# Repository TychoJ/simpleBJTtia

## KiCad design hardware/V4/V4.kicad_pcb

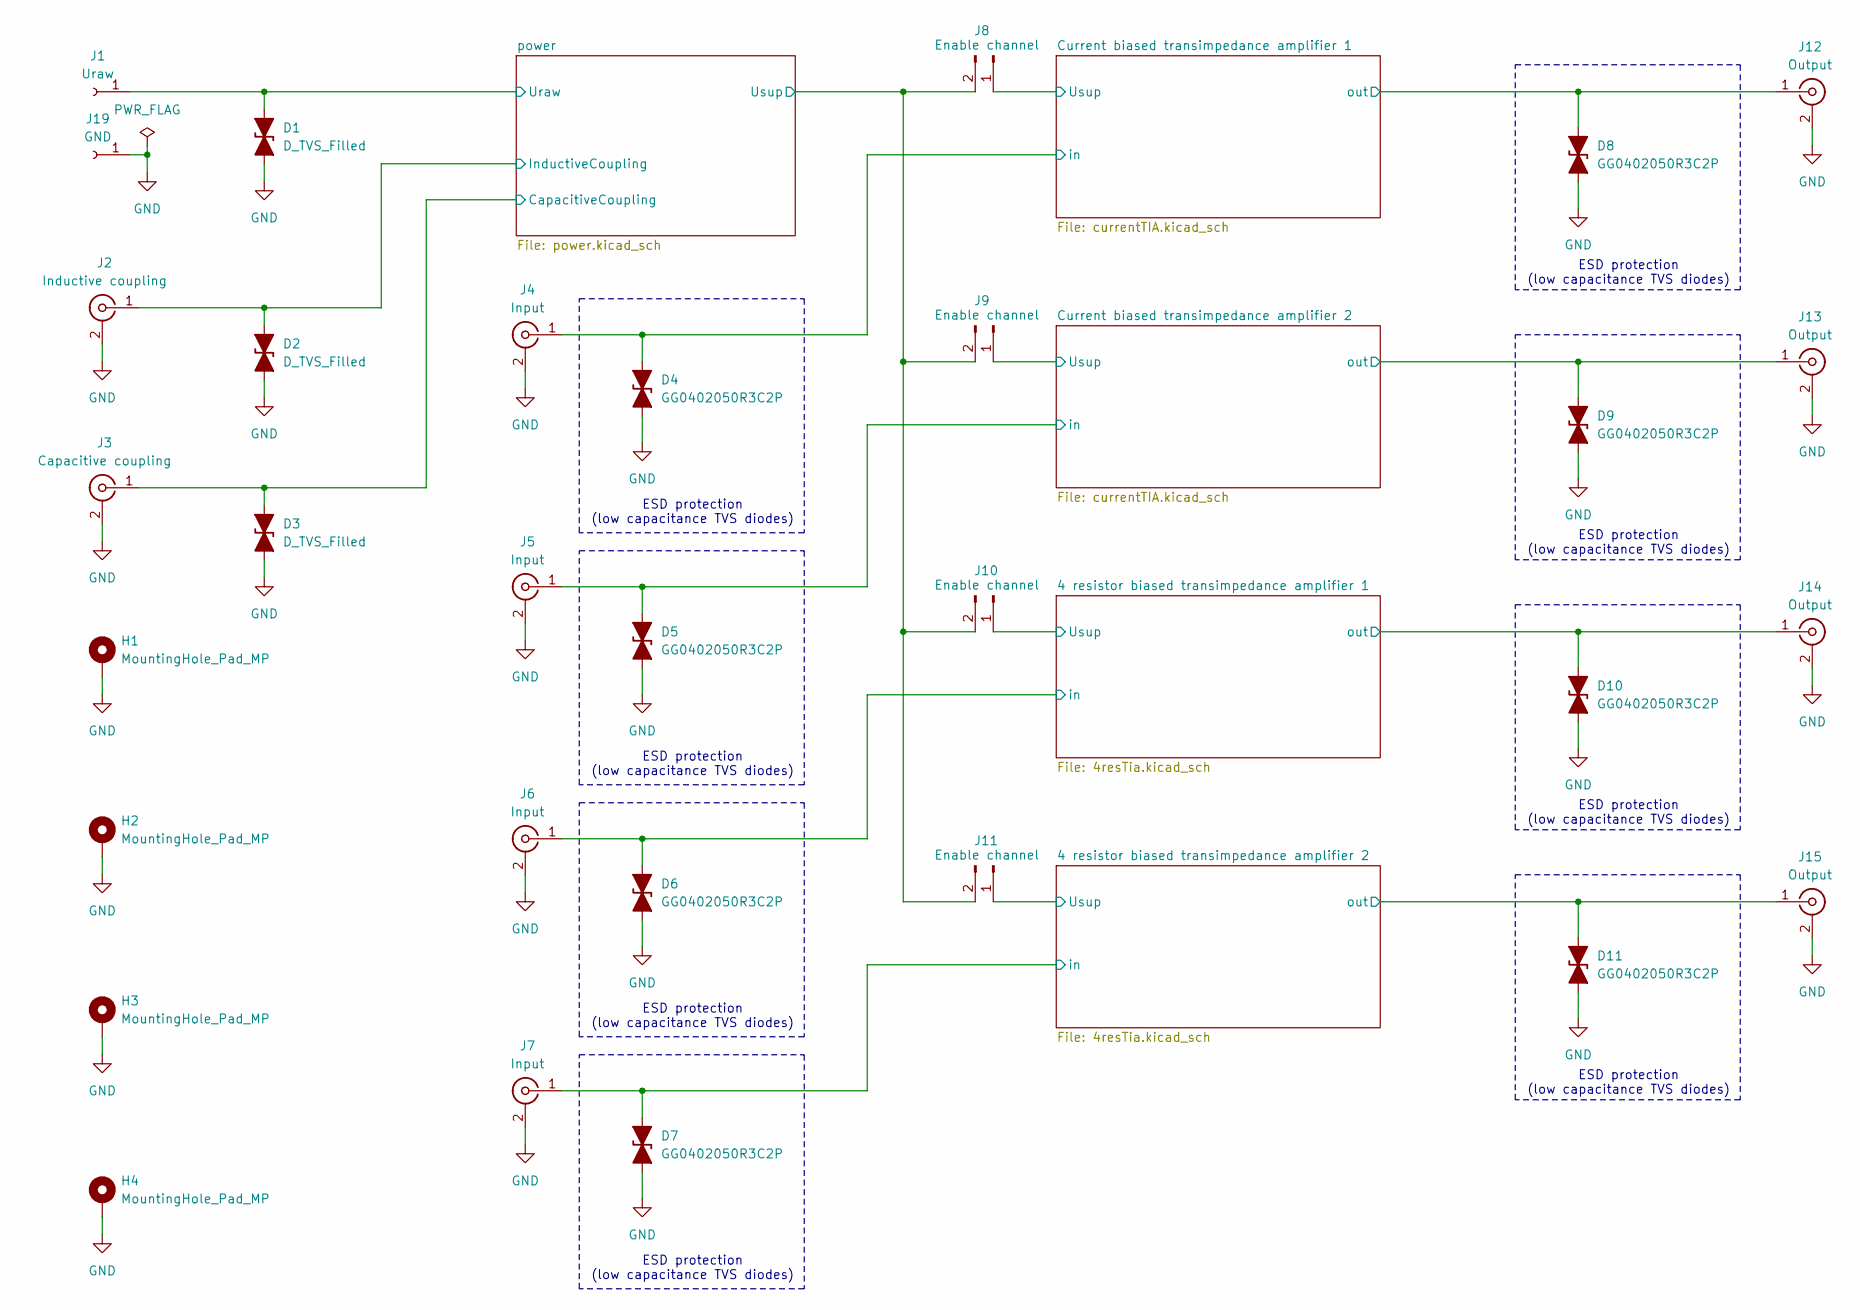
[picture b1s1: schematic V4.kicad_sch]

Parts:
D1, D2, D3: D_TVS_Filled; D_0805_2012Metric
D4, D5, D6, D7, D8, D9, D10, D11: GG0402050R3C2P; D_0402_1005Metric_Pad0.77x0.64mm_HandSolder
H1, H2, H3, H4: MountingHole_Pad_MP; MountingHole_4.3mm_M4_Pad_Via
J1: Uraw; Banana_Jack_1Pin
J2: Inductive coupling; BNC_Amphenol_B6252HB-NPP3G-50_Horizontal
J3: Capacitive coupling; BNC_Amphenol_B6252HB-NPP3G-50_Horizontal
J4, J5, J6, J7: Input; BNC_Amphenol_B6252HB-NPP3G-50_Horizontal
J8, J9, J10, J11: Enable channel; PinHeader_1x02_P2.54mm_Vertical
J12, J13, J14, J15: Output; BNC_Amphenol_B6252HB-NPP3G-50_Horizontal
J19: GND; Banana_Jack_1Pin

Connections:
/4 resistor biased transimpedance amplifier 1/Usup: J10.1; also elsewhere on the board
/4 resistor biased transimpedance amplifier 1/in: D6.2 (A2), J6.1 (In); also elsewhere on the board
/4 resistor biased transimpedance amplifier 1/out: D10.2 (A2), J14.1 (In); also elsewhere on the board
/4 resistor biased transimpedance amplifier 2/Usup: J11.1; also elsewhere on the board
/4 resistor biased transimpedance amplifier 2/in: D7.2 (A2), J7.1 (In); also elsewhere on the board
/4 resistor biased transimpedance amplifier 2/out: D11.2 (A2), J15.1 (In); also elsewhere on the board
/Current biased transimpedance amplifier 1/Usup: J8.1; also elsewhere on the board
/Current biased transimpedance amplifier 1/in: D4.2 (A2), J4.1 (In); also elsewhere on the board
/Current biased transimpedance amplifier 1/out: D8.2 (A2), J12.1 (In); also elsewhere on the board
/Current biased transimpedance amplifier 2/Usup: J9.1; also elsewhere on the board
/Current biased transimpedance amplifier 2/in: D5.2 (A2), J5.1 (In); also elsewhere on the board
/Current biased transimpedance amplifier 2/out: D9.2 (A2), J13.1 (In); also elsewhere on the board
/power/CapacitiveCoupling: D3.2 (A2), J3.1 (In); also elsewhere on the board
/power/InductiveCoupling: D2.2 (A2), J2.1 (In); also elsewhere on the board
/power/Uraw: D1.2 (A2), J1.1; also elsewhere on the board
/power/Usup: J8.2, J9.2, J10.2, J11.2; also elsewhere on the board
GND: D1.1 (A1), D2.1 (A1), D3.1 (A1), D4.1 (A1), D5.1 (A1), D6.1 (A1), D7.1 (A1), D8.1 (A1), D9.1 (A1), D10.1 (A1), D11.1 (A1), H1.MP, H2.MP, H3.MP, H4.MP, J2.2 (Ext), J3.2 (Ext), J4.2 (Ext), J5.2 (Ext), J6.2 (Ext), J7.2 (Ext), J12.2 (Ext), J13.2 (Ext), J14.2 (Ext), J15.2 (Ext), J19.1; also elsewhere on the board

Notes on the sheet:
ESD protection (low capacitance TVS diodes)

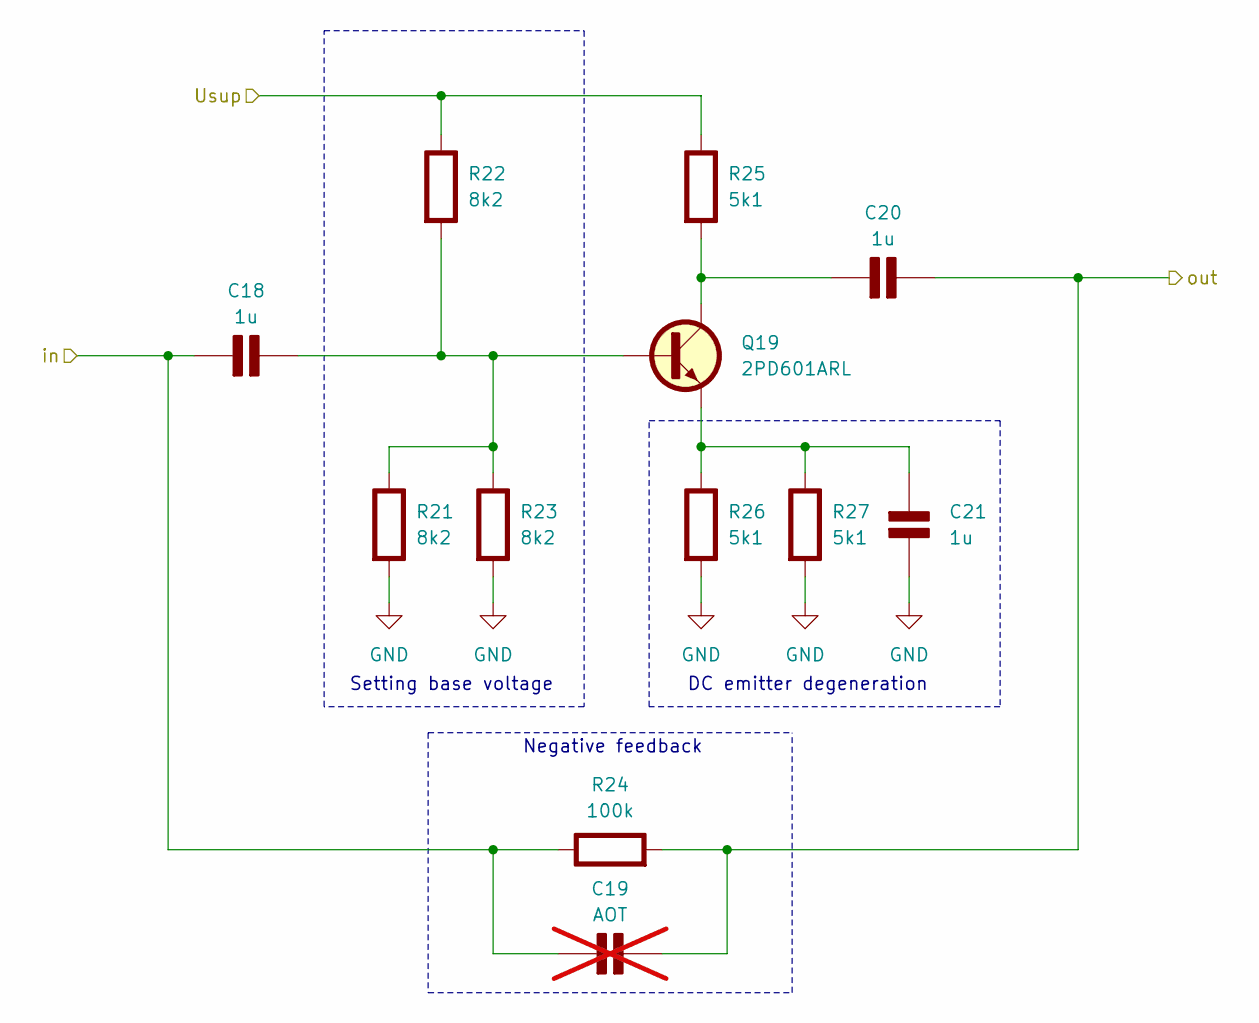
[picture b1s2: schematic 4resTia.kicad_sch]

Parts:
C18, C20, C21: 1u; C_0805_2012Metric; Rating V
C19: AOT; C_0805_2012Metric; Rating V; not fitted
Q19: 2PD601ARL; SOT-23
R21, R22, R23: 8k2; R_0805_2012Metric; Rating W
R24: 100k; R_0805_2012Metric; Rating W
R25, R26, R27: 5k1; R_0805_2012Metric; Rating W

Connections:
/4 resistor biased transimpedance amplifier 1/Usup: R22.1 (+), R25.1 (+); also elsewhere on the board
/4 resistor biased transimpedance amplifier 1/in: C18.1 (+), C19.1 (+), R24.1 (+); also elsewhere on the board
/4 resistor biased transimpedance amplifier 1/out: C19.2 (-), C20.2 (-), R24.2 (-); also elsewhere on the board
GND: C21.2 (-), R21.2 (-), R23.2 (-), R26.2 (-), R27.2 (-); also elsewhere on the board
unnamed: C18.2 (-), Q19.1 (B), R21.1 (+), R22.2 (-), R23.1 (+)
unnamed: C20.1 (+), Q19.3 (C), R25.2 (-)
unnamed: C21.1 (+), Q19.2 (E), R26.1 (+), R27.1 (+)

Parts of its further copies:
C22, C24, C25: 1u; C_0805_2012Metric; Rating V
C23: AOT; C_0805_2012Metric; Rating V; not fitted
Q20: 2PD601ARL; SOT-23
R28, R29, R30: 8k2; R_0805_2012Metric; Rating W
R31: 100k; R_0805_2012Metric; Rating W
R32, R33, R34: 5k1; R_0805_2012Metric; Rating W

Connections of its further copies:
/4 resistor biased transimpedance amplifier 2/Usup: R29.1 (+), R32.1 (+); also elsewhere on the board
/4 resistor biased transimpedance amplifier 2/in: C22.1 (+), C23.1 (+), R31.1 (+); also elsewhere on the board
/4 resistor biased transimpedance amplifier 2/out: C23.2 (-), C24.2 (-), R31.2 (-); also elsewhere on the board
GND: C25.2 (-), R28.2 (-), R30.2 (-), R33.2 (-), R34.2 (-); also elsewhere on the board
unnamed: C22.2 (-), Q20.1 (B), R28.1 (+), R29.2 (-), R30.1 (+)
unnamed: C24.1 (+), Q20.3 (C), R32.2 (-)
unnamed: C25.1 (+), Q20.2 (E), R33.1 (+), R34.1 (+)

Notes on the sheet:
DC emitter degeneration
Negative feedback
Setting base voltage

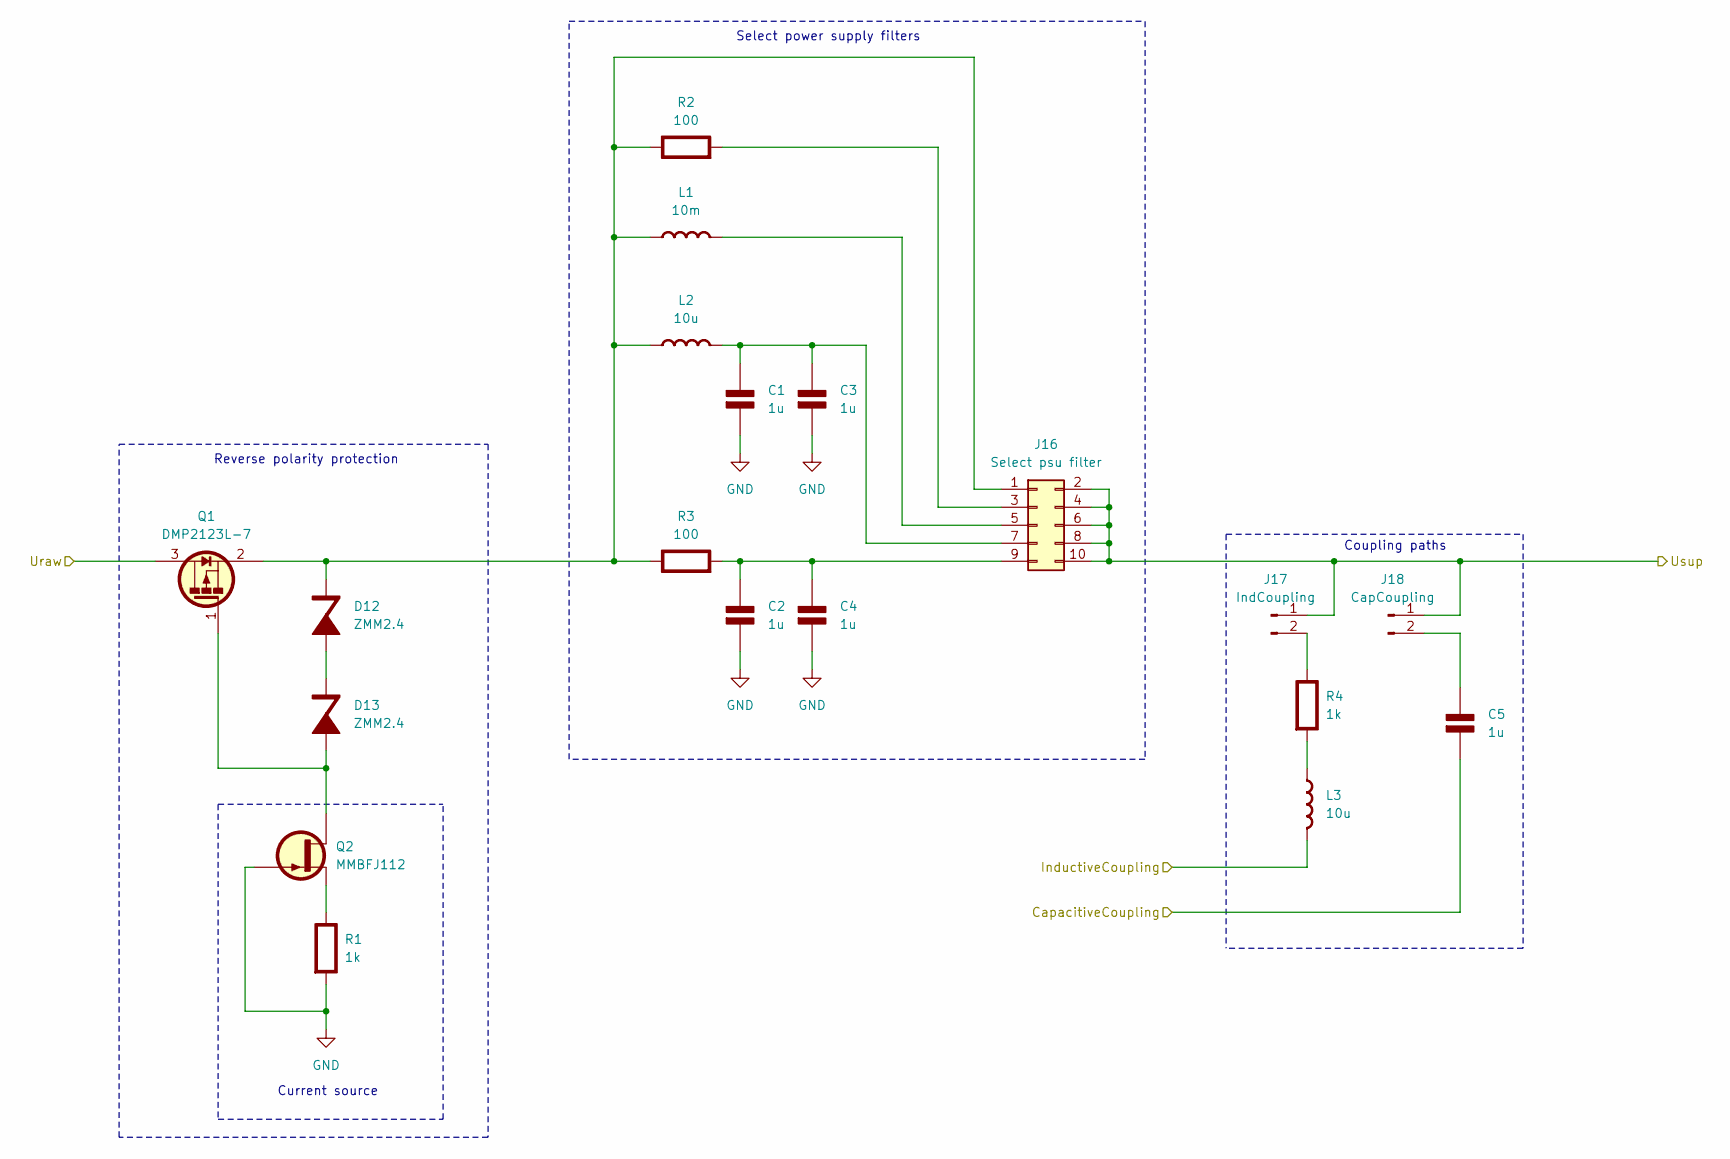
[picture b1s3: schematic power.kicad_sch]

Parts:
C1, C2, C3, C4, C5: 1u; C_0805_2012Metric; Rating V
D12, D13: ZMM2.4; D_MicroMELF
J16: Select psu filter; PinHeader_2x05_P2.54mm_Vertical
J17: IndCoupling; PinHeader_1x02_P2.54mm_Vertical
J18: CapCoupling; PinHeader_1x02_P2.54mm_Vertical
L1: 10m; L_12x12mm_H8mm; Rating A
L2, L3: 10u; L_12x12mm_H8mm; Rating A
Q1: DMP2123L-7; SOT-23
Q2: MMBFJ112; SOT-23
R1, R4: 1k; R_0805_2012Metric; Rating W
R2, R3: 100; R_0805_2012Metric; Rating W

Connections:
/power/CapacitiveCoupling: C5.2 (-); also elsewhere on the board
/power/InductiveCoupling: L3.2 (-); also elsewhere on the board
/power/Uraw: Q1.3 (D); also elsewhere on the board
/power/Usup: J16.2, J16.4, J16.6, J16.8, J16.10, J17.1, J18.1; also elsewhere on the board
GND: C1.2 (-), C2.2 (-), C3.2 (-), C4.2 (-), Q2.3 (G), R1.2 (-); also elsewhere on the board
unnamed: C1.1 (+), C3.1 (+), J16.7, L2.2 (-)
unnamed: C2.1 (+), C4.1 (+), J16.9, R3.2 (-)
unnamed: C5.1 (+), J18.2
unnamed: D12.2 (A), D13.1 (K)
unnamed: D12.1 (K), J16.1, L1.1 (+), L2.1 (+), Q1.2 (S), R2.1 (+), R3.1 (+)
unnamed: D13.2 (A), Q1.1 (G), Q2.1 (D)
unnamed: J16.3, R2.2 (-)
unnamed: J16.5, L1.2 (-)
unnamed: J17.2, R4.1 (+)
unnamed: L3.1 (+), R4.2 (-)
unnamed: Q2.2 (S), R1.1 (+)

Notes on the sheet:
Reverse polarity protection
Coupling paths
Current source
Select power supply filters

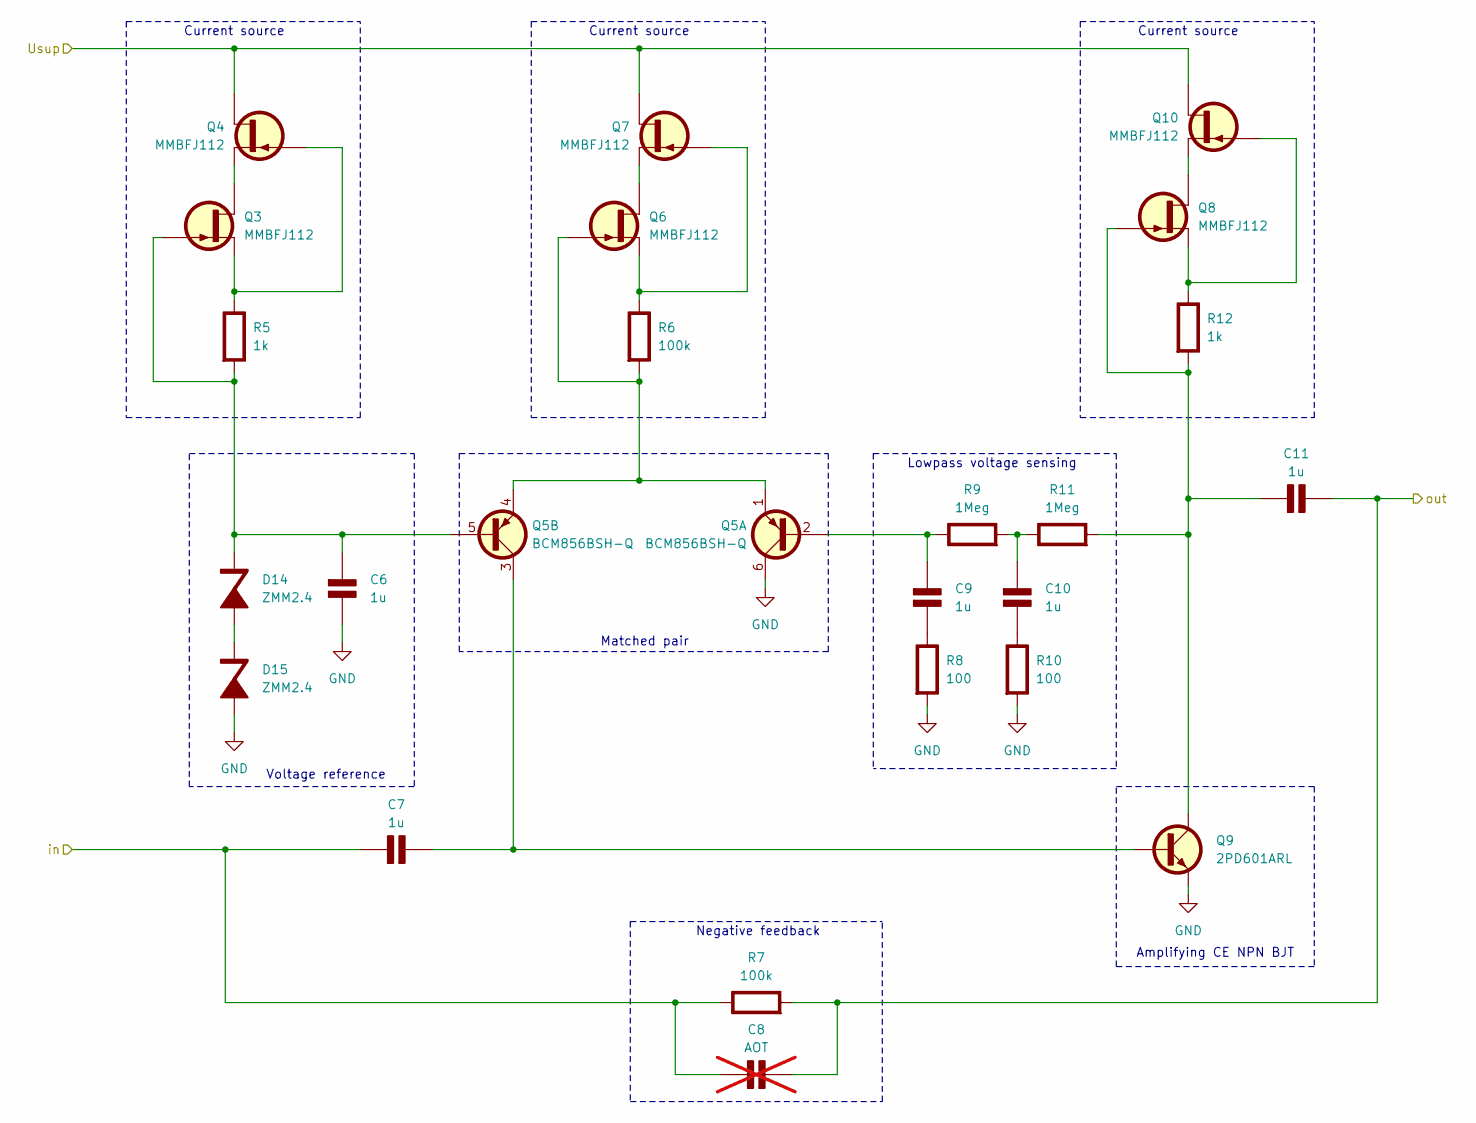
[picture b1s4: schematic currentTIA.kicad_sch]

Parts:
C6, C7, C9, C10, C11: 1u; C_0805_2012Metric; Rating V
C8: AOT; C_0805_2012Metric; Rating V; not fitted
D14, D15: ZMM2.4; D_MicroMELF
Q3, Q4, Q6, Q7, Q8, Q10: MMBFJ112; SOT-23
Q5: BCM856BSH-Q; TSOP-6_1.65x3.05mm_P0.95mm
Q9: 2PD601ARL; SOT-23
R5, R12: 1k; R_0805_2012Metric; Rating W
R6, R7: 100k; R_0805_2012Metric; Rating W
R8, R10: 100; R_0805_2012Metric; Rating W
R9, R11: 1Meg; R_0805_2012Metric; Rating W

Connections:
/Current biased transimpedance amplifier 1/Usup: Q4.1 (D), Q7.1 (D), Q10.1 (D); also elsewhere on the board
/Current biased transimpedance amplifier 1/in: C7.1 (+), C8.1 (+), R7.1 (+); also elsewhere on the board
/Current biased transimpedance amplifier 1/out: C8.2 (-), C11.2 (-), R7.2 (-); also elsewhere on the board
GND: C6.2 (-), D15.2 (A), Q5.6, Q9.2 (E), R8.2 (-), R10.2 (-); also elsewhere on the board
unnamed: C6.1 (+), D14.1 (K), Q3.3 (G), Q5.5, R5.2 (-)
unnamed: C7.2 (-), Q5.3, Q9.1 (B)
unnamed: C9.1 (+), Q5.2, R9.1 (+)
unnamed: C9.2 (-), R8.1 (+)
unnamed: C10.1 (+), R9.2 (-), R11.1 (+)
unnamed: C10.2 (-), R10.1 (+)
unnamed: C11.1 (+), Q8.3 (G), Q9.3 (C), R11.2 (-), R12.2 (-)
unnamed: D14.2 (A), D15.1 (K)
unnamed: Q3.1 (D), Q4.2 (S)
unnamed: Q3.2 (S), Q4.3 (G), R5.1 (+)
unnamed: Q6.1 (D), Q7.2 (S)
unnamed: Q5.1, Q5.4, Q6.3 (G), R6.2 (-)
unnamed: Q6.2 (S), Q7.3 (G), R6.1 (+)
unnamed: Q8.2 (S), Q10.3 (G), R12.1 (+)
unnamed: Q8.1 (D), Q10.2 (S)

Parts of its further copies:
C12, C13, C15, C16, C17: 1u; C_0805_2012Metric; Rating V
C14: AOT; C_0805_2012Metric; Rating V; not fitted
D16, D17: ZMM2.4; D_MicroMELF
Q11, Q12, Q14, Q15, Q16, Q18: MMBFJ112; SOT-23
Q13: BCM856BSH-Q; TSOP-6_1.65x3.05mm_P0.95mm
Q17: 2PD601ARL; SOT-23
R13, R20: 1k; R_0805_2012Metric; Rating W
R14, R15: 100k; R_0805_2012Metric; Rating W
R16, R18: 100; R_0805_2012Metric; Rating W
R17, R19: 1Meg; R_0805_2012Metric; Rating W

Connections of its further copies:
/Current biased transimpedance amplifier 2/Usup: Q12.1 (D), Q15.1 (D), Q18.1 (D); also elsewhere on the board
/Current biased transimpedance amplifier 2/in: C13.1 (+), C14.1 (+), R15.1 (+); also elsewhere on the board
/Current biased transimpedance amplifier 2/out: C14.2 (-), C17.2 (-), R15.2 (-); also elsewhere on the board
GND: C12.2 (-), D17.2 (A), Q13.6, Q17.2 (E), R16.2 (-), R18.2 (-); also elsewhere on the board
unnamed: C12.1 (+), D16.1 (K), Q11.3 (G), Q13.5, R13.2 (-)
unnamed: C13.2 (-), Q13.3, Q17.1 (B)
unnamed: C15.1 (+), Q13.2, R17.1 (+)
unnamed: C15.2 (-), R16.1 (+)
unnamed: C16.1 (+), R17.2 (-), R19.1 (+)
unnamed: C16.2 (-), R18.1 (+)
unnamed: C17.1 (+), Q16.3 (G), Q17.3 (C), R19.2 (-), R20.2 (-)
unnamed: D16.2 (A), D17.1 (K)
unnamed: Q11.1 (D), Q12.2 (S)
unnamed: Q11.2 (S), Q12.3 (G), R13.1 (+)
unnamed: Q14.1 (D), Q15.2 (S)
unnamed: Q13.1, Q13.4, Q14.3 (G), R14.2 (-)
unnamed: Q14.2 (S), Q15.3 (G), R14.1 (+)
unnamed: Q16.1 (D), Q18.2 (S)
unnamed: Q16.2 (S), Q18.3 (G), R20.1 (+)

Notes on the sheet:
Matched pair
Negative feedback
Amplifying CE NPN BJT
Voltage reference
Current source
Lowpass voltage sensing

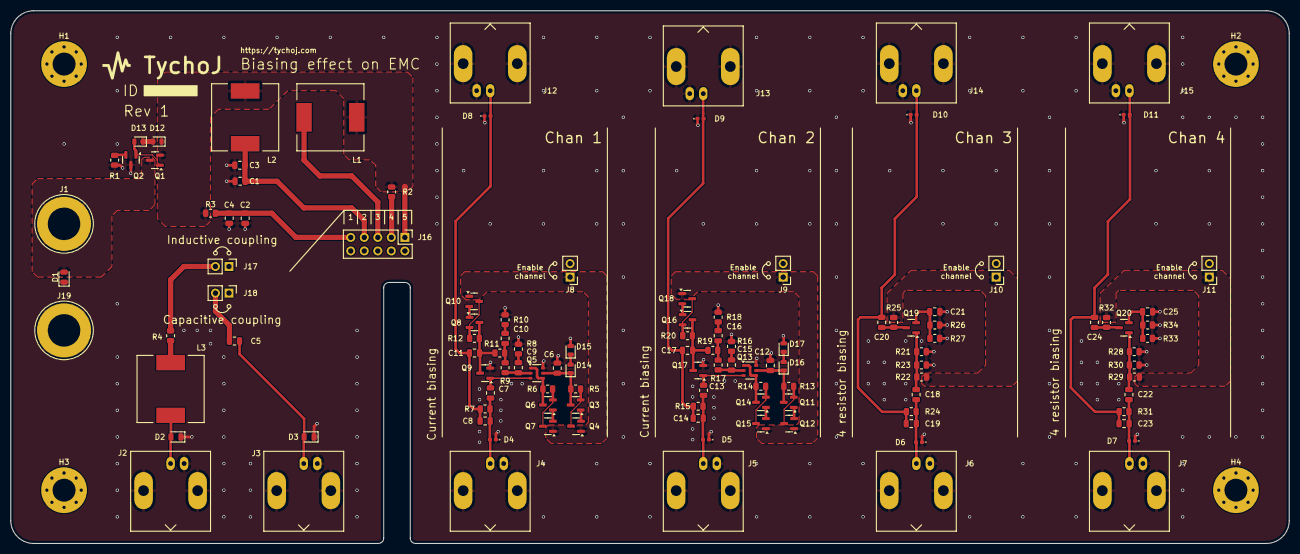
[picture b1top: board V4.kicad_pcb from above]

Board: 4 copper layers, 240.0 x 100.0 mm, 122 parts (0 on the bottom side), 64 nets.

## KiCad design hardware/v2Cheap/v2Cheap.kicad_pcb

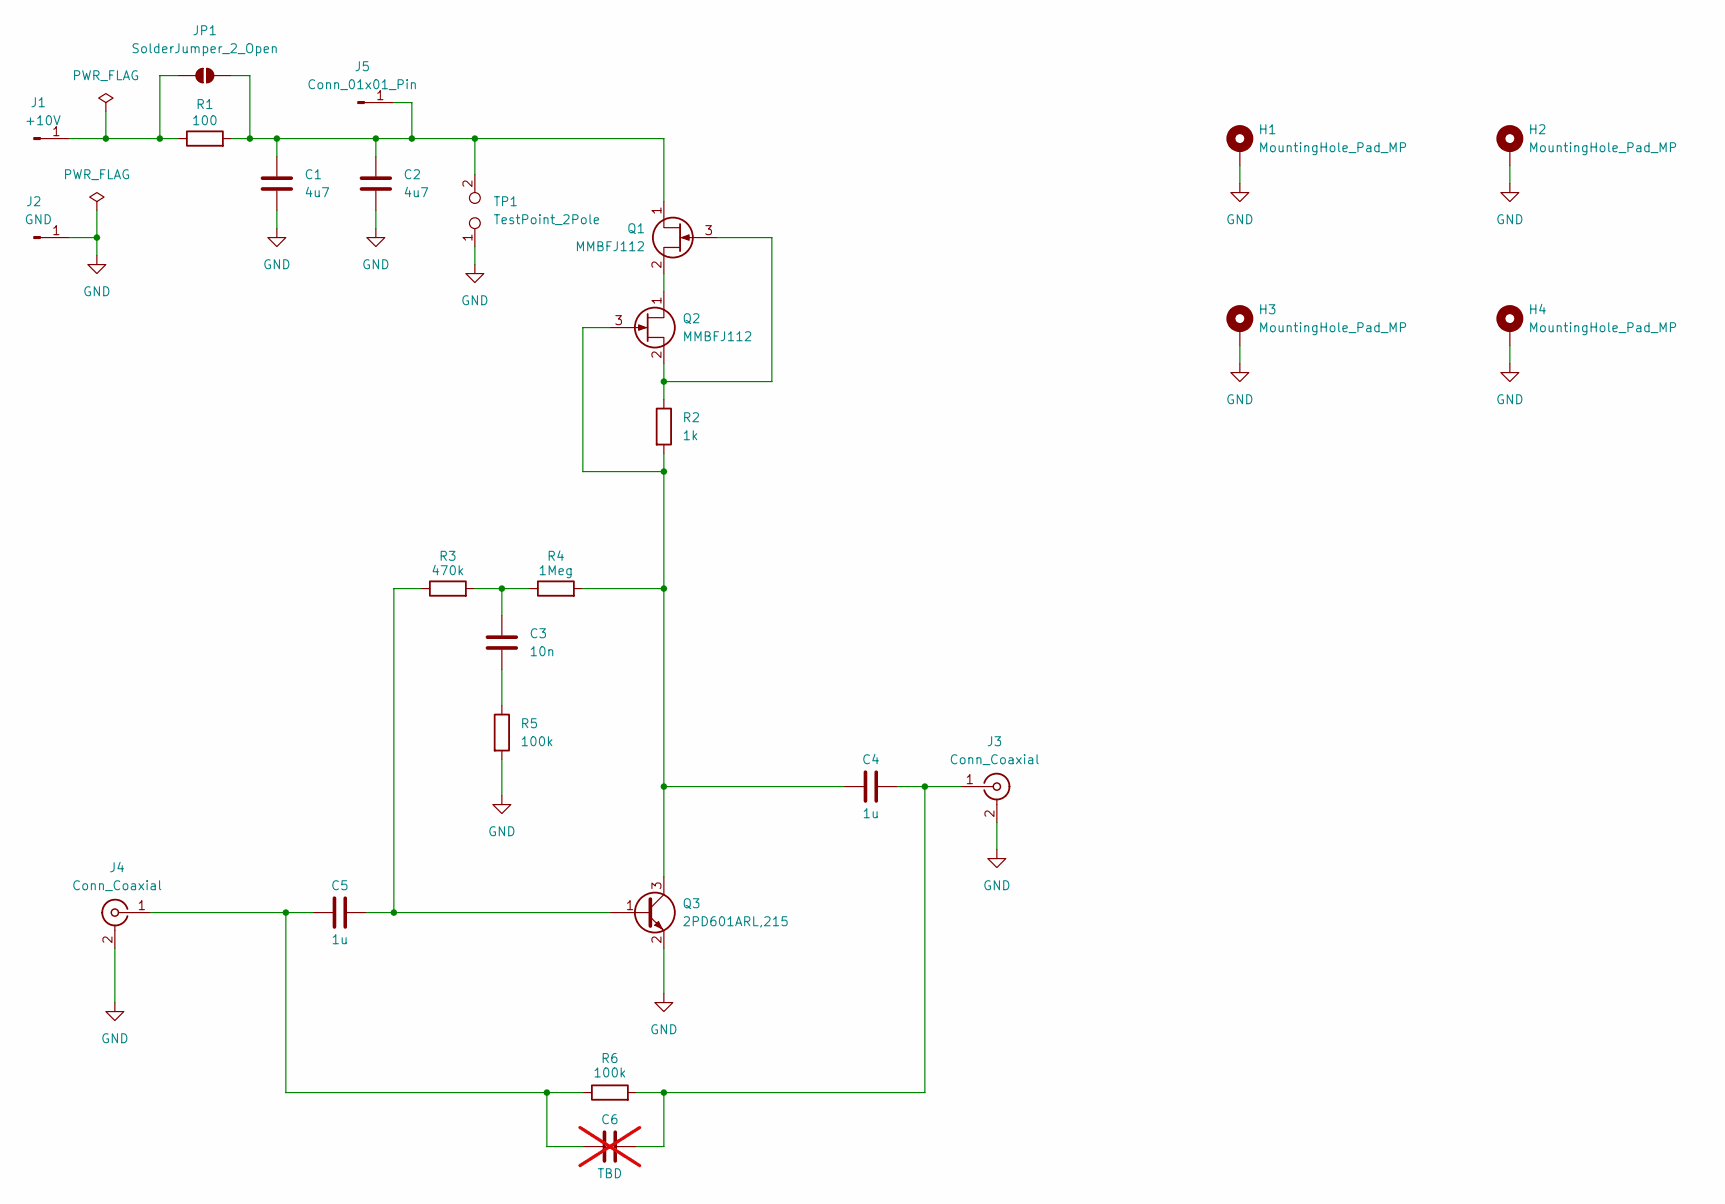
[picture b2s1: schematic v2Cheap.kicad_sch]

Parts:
C1, C2: 4u7; C_1206_3216Metric; LCSC C29823
C3: 10n; C_0805_2012Metric; LCSC C1710
C4, C5: 1u; C_0805_2012Metric; LCSC C28323
C6: TBD; C_0603_1608Metric; not fitted
H1, H2, H3, H4: MountingHole_Pad_MP; MountingHole_3mm_Pad_Via
J1: +10V; PinHeader_1x01_P2.54mm_Vertical
J2: GND; PinHeader_1x01_P2.54mm_Vertical
J3, J4: Conn_Coaxial; C2837587; LCSC C2837587
J5: Conn_01x01_Pin; PinHeader_1x01_P2.54mm_Vertical
JP1: SolderJumper_2_Open; SolderJumper-2_P1.3mm_Open_RoundedPad1.0x1.5mm
Q1, Q2: MMBFJ112; SOT-23; LCSC C258195
Q3: 2PD601ARL,215; SOT-23; LCSC C554106
R1: 100; R_0805_2012Metric; LCSC C17408
R2: 1k; R_0805_2012Metric; LCSC C110774
R3: 470k; R_0805_2012Metric; LCSC C218589
R4: 1Meg; R_0805_2012Metric; LCSC C218408
R5, R6: 100k; R_0805_2012Metric; LCSC C122537
TP1: TestPoint_2Pole; TestPoint_2Pads_Pitch2.54mm_Drill0.8mm

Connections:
GND: C1.1, C2.1, H1.1 (MP), H2.1 (MP), H3.1 (MP), H4.1 (MP), J2.1, J3.2 (Ext), J4.2 (Ext), Q3.2 (E), R5.2, TP1.1
unnamed: C3.1, R3.2, R4.1
unnamed: C3.2, R5.1
unnamed: J1.1, JP1.1 (A), R1.1
unnamed: C4.1, C6.1, J3.1 (In), R6.2
unnamed: C5.2, C6.2, J4.1 (In), R6.1
unnamed: C1.2, C2.2, J5.1, JP1.2 (B), Q1.1 (D), R1.2, TP1.2
unnamed: Q1.3 (G), Q2.2 (S), R2.1
unnamed: Q1.2 (S), Q2.1 (D)
unnamed: C4.2, Q2.3 (G), Q3.3 (C), R2.2, R4.2
unnamed: C5.1, Q3.1 (B), R3.1

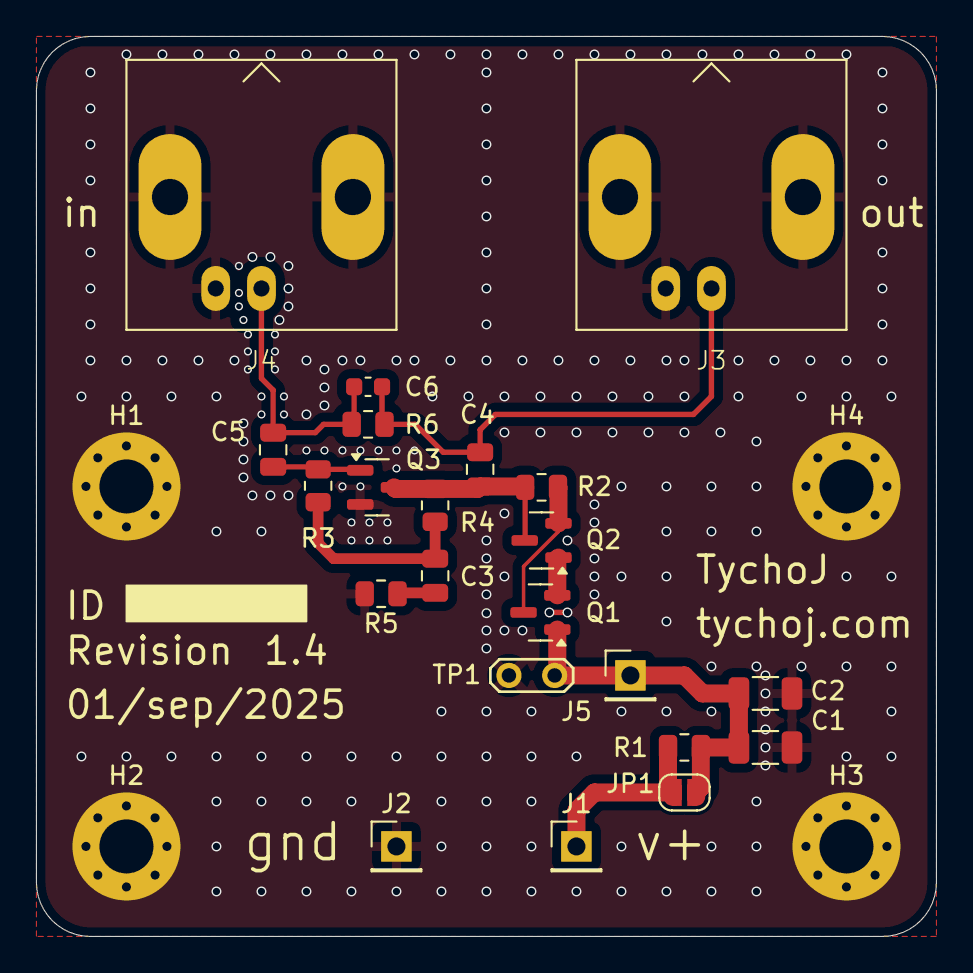
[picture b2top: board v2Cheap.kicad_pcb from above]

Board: 2 copper layers, 50.0 x 50.0 mm, 26 parts (0 on the bottom side), 11 nets.

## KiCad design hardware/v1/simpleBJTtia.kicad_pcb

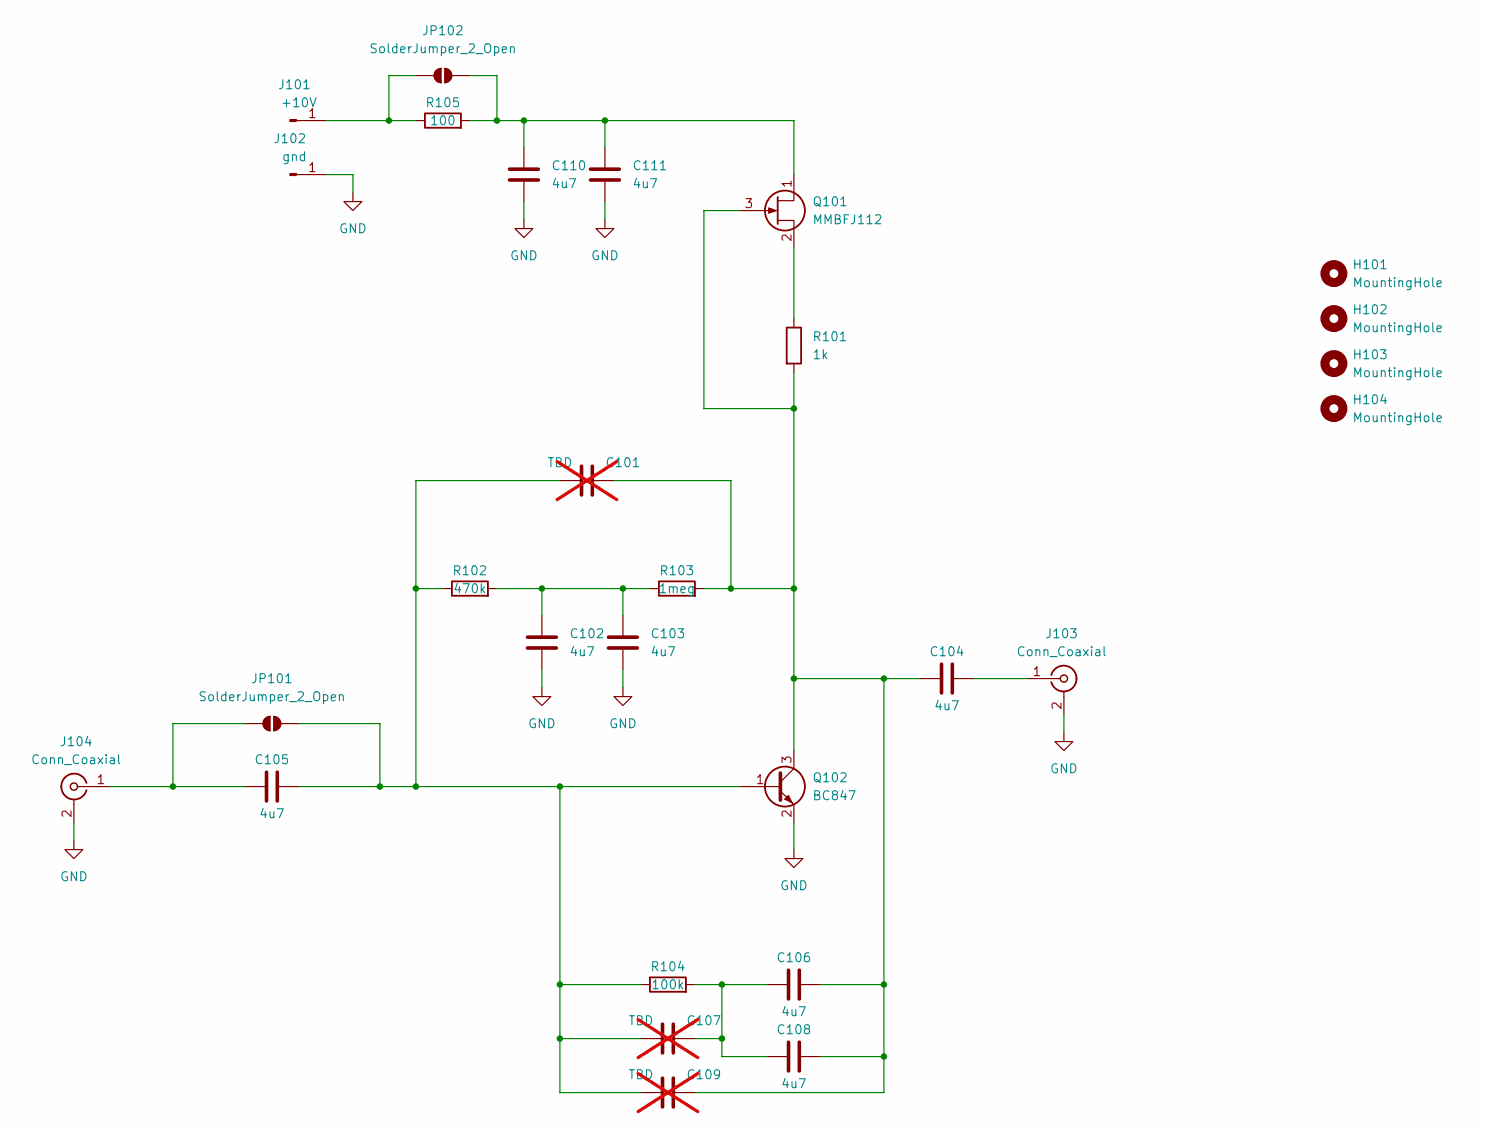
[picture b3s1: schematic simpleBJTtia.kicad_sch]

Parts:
C101, C107, C109: TBD; C_0805_2012Metric; not fitted
C102, C103, C104, C105, C106, C108, C110, C111: 4u7; C_Rect_L7.2mm_W5.5mm_P5.00mm_FKS2_FKP2_MKS2_MKP2
H101, H102, H103, H104: MountingHole; MountingHole_3mm
J101: +10V; CT3149-2
J102: gnd; CT3149-0
J103, J104: Conn_Coaxial; BNC_Amphenol_B6252HB-NPP3G-50_Horizontal
JP101, JP102: SolderJumper_2_Open; SolderJumper-2_P1.3mm_Open_RoundedPad1.0x1.5mm
Q101: MMBFJ112; SOT-23
Q102: BC847; SOT-23
R101: 1k; R_0805_2012Metric
R102: 470k; R_0805_2012Metric
R103: 1meg; R_0805_2012Metric
R104: 100k; R_0805_2012Metric
R105: 100; R_0805_2012Metric

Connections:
GND: C102.1, C103.1, C110.1, C111.1, J102.1, J103.2 (Ext), J104.2 (Ext), Q102.2 (E)
unnamed: C102.2, C103.2, R102.2, R103.1
unnamed: C106.2, C107.2, C108.2, R104.2
unnamed: J101.1, JP102.1 (A), R105.1
unnamed: C104.1, J103.1 (In)
unnamed: C105.2, J104.1 (In), JP101.1 (A)
unnamed: C101.1, C105.1, C107.1, C109.1, JP101.2 (B), Q102.1 (B), R102.1, R104.1
unnamed: C110.2, C111.2, JP102.2 (B), Q101.1 (D), R105.2
unnamed: C101.2, C104.2, C106.1, C108.1, C109.2, Q101.3 (G), Q102.3 (C), R101.2, R103.2
unnamed: Q101.2 (S), R101.1

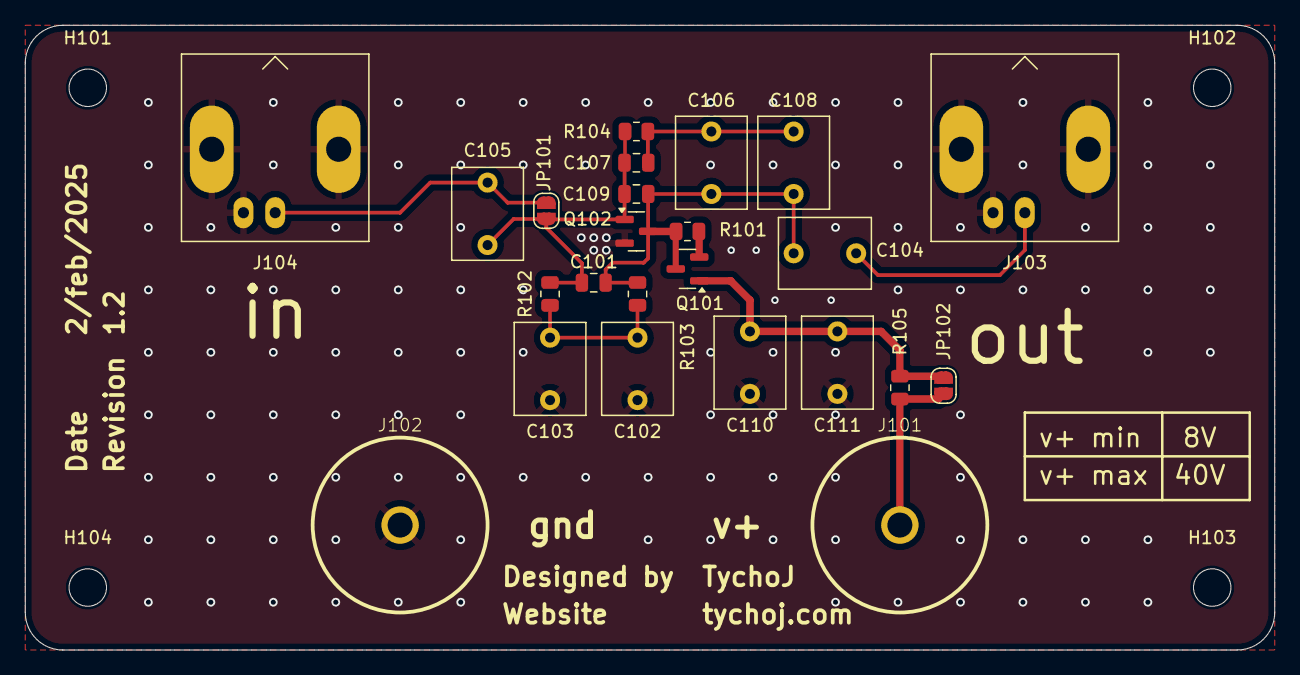
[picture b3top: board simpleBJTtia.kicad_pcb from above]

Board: 2 copper layers, 100.0 x 50.0 mm, 28 parts (0 on the bottom side), 10 nets.

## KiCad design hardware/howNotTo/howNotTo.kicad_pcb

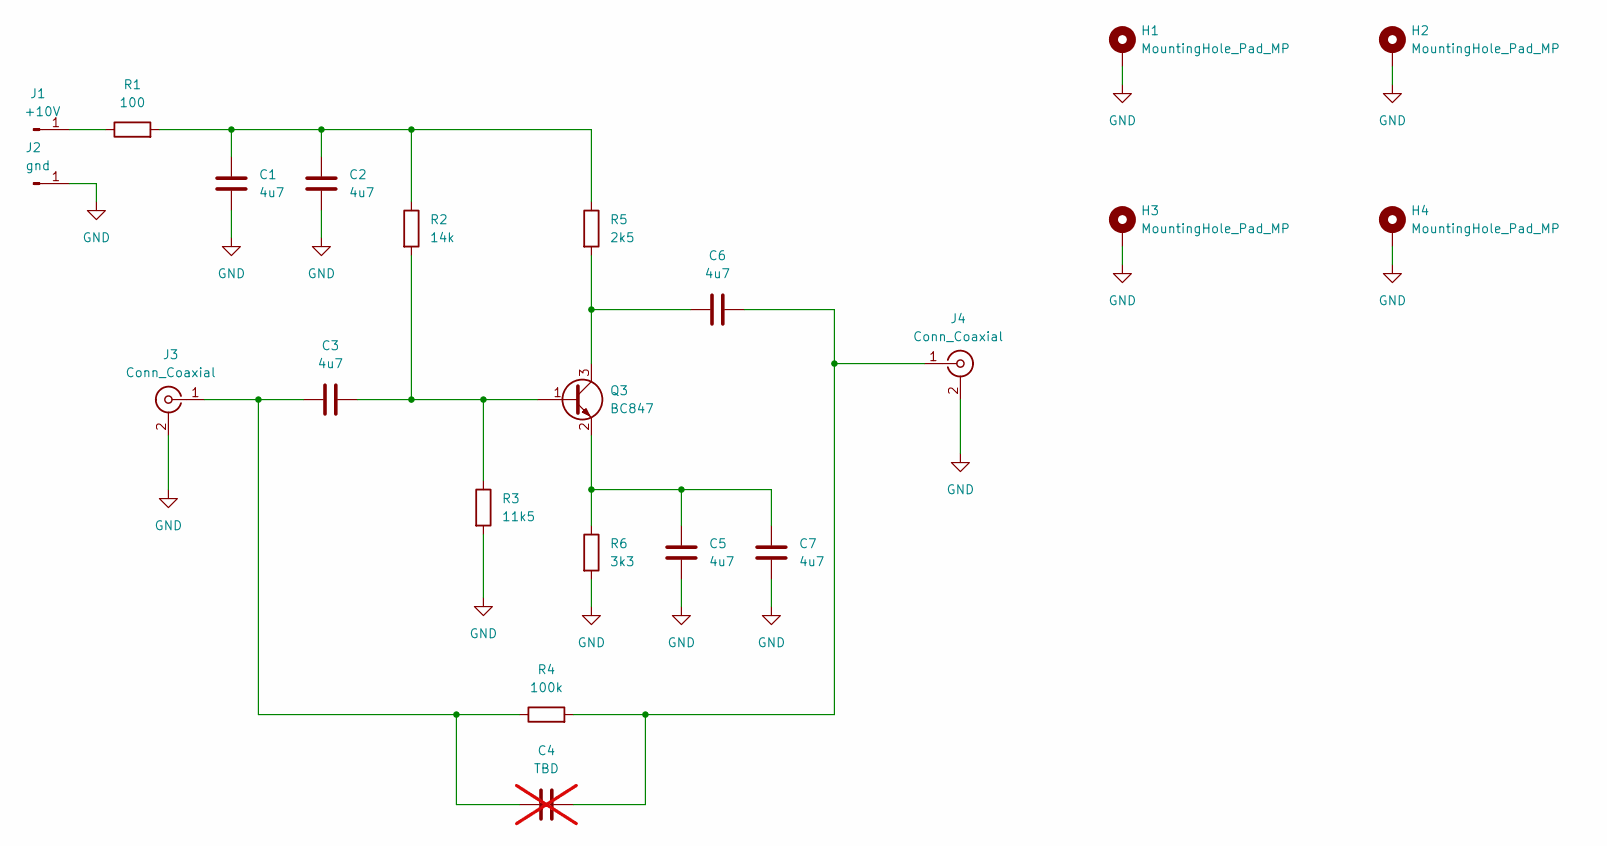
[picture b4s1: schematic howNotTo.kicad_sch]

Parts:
C1, C2, C3, C5, C6, C7: 4u7; C_Rect_L7.2mm_W5.5mm_P5.00mm_FKS2_FKP2_MKS2_MKP2
C4: TBD; C_0805_2012Metric; not fitted
H1, H2, H3, H4: MountingHole_Pad_MP; MountingHole_3mm_Pad_Via
J1: +10V; CT3149-2
J2: gnd; CT3149-0
J3, J4: Conn_Coaxial; BNC_Amphenol_B6252HB-NPP3G-50_Horizontal
Q3: BC847; SOT-23
R1: 100; R_0805_2012Metric
R2: 14k; R_0805_2012Metric
R3: 11k5; R_0805_2012Metric
R4: 100k; R_0805_2012Metric
R5: 2k5; R_0805_2012Metric
R6: 3k3; R_0805_2012Metric

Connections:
GND: C1.1, C2.1, C5.2, C7.2, H1.1 (MP), H2.1 (MP), H3.1 (MP), H4.1 (MP), J2.1, J3.2 (Ext), J4.2 (Ext), R3.2, R6.2
unnamed: C1.2, C2.2, R1.2, R2.1, R5.1
unnamed: J1.1, R1.1
unnamed: C3.1, C4.1, J3.1 (In), R4.1
unnamed: C4.2, C6.2, J4.1 (In), R4.2
unnamed: C3.2, Q3.1 (B), R2.2, R3.1
unnamed: C6.1, Q3.3 (C), R5.2
unnamed: C5.1, C7.1, Q3.2 (E), R6.1
